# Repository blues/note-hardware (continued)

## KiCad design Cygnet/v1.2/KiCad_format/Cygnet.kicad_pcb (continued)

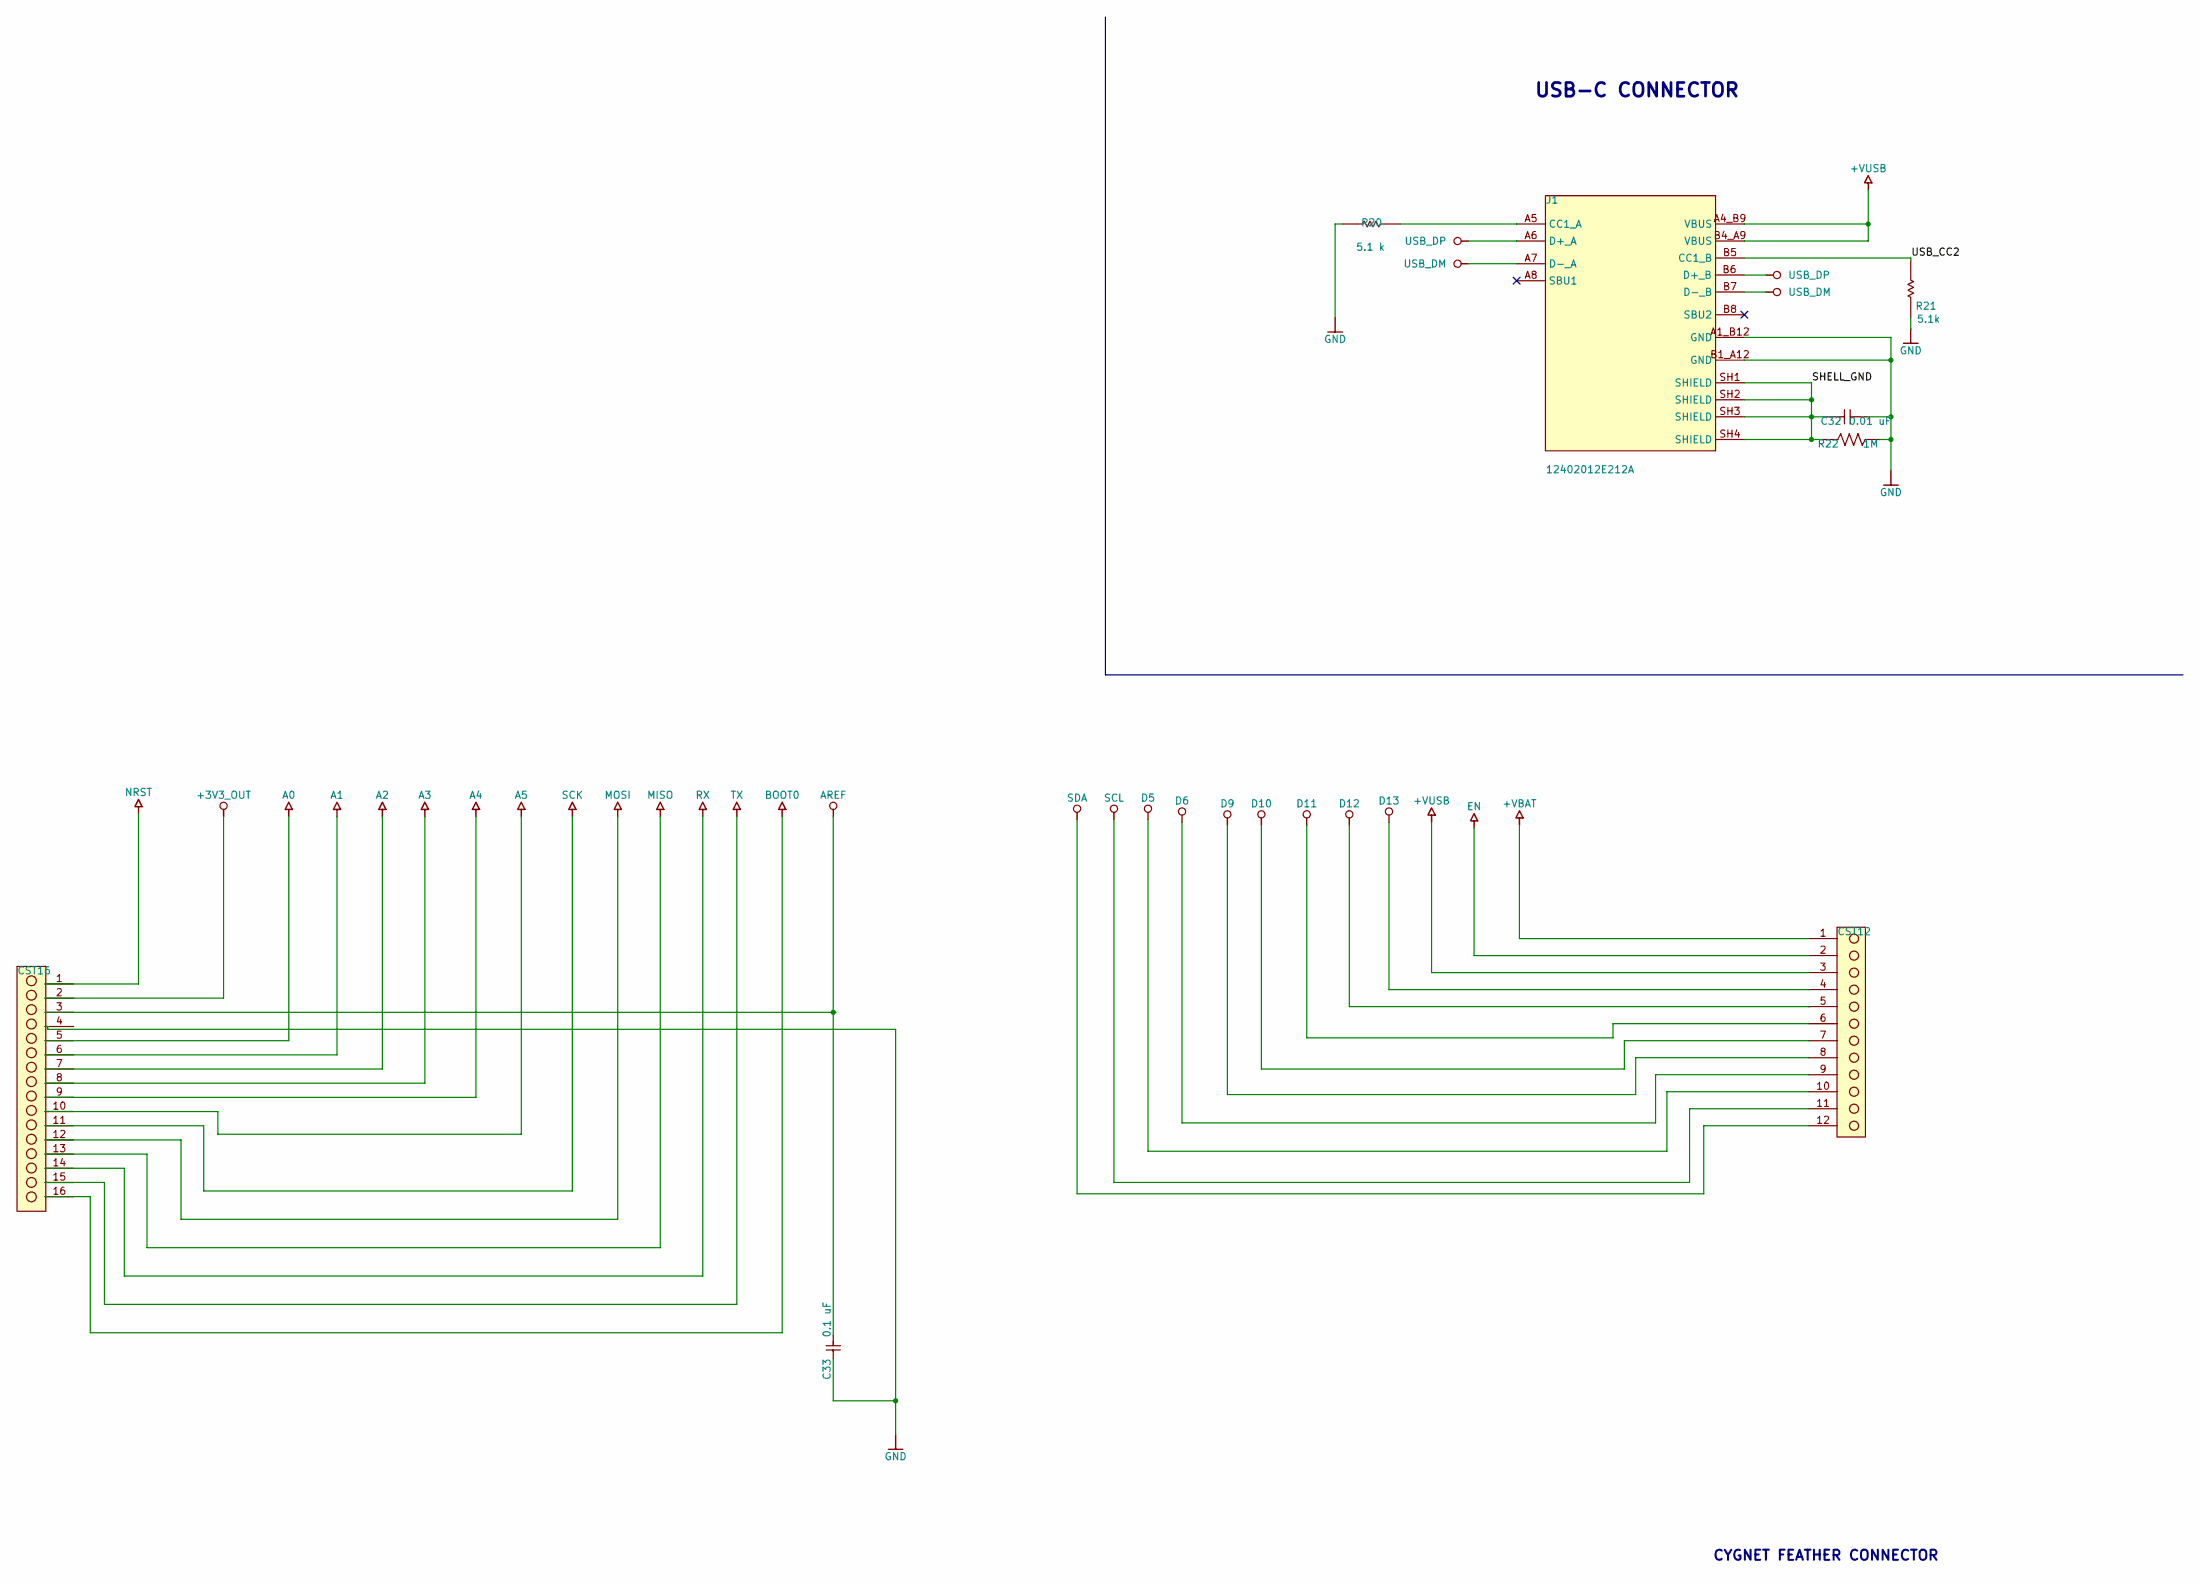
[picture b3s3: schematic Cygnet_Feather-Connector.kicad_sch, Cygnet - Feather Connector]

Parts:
C32: 0.01 uF; CS1206KKX7RCBB103-Footprint-1; MPN CS1206KKX7RCBB103
C33: 0.1 uF; FP-CC0402-MFG; MPN CC0402KRX7R7BB104
CST12: 12 pin castellated hole 1.6mm/ 1mm; 12 pin castellated hole 1.6mm_ 1mm-Footprint-1
CST16: 16 pin castellations 1.6mm/ 1mm; castellations 1mm_ 0.7mm-Footprint-1
J1: 12402012E212A; AMPHENOL_12402012E212A; MPN 12402012E212A
R20: 5.1 k; RESC1005X40X25NL05T10; MPN RC0402JR-075K1L
R21: 5.1k; RESC1005X40X25NL05T10; MPN RC0402JR-075K1L
R22: 1M; RC1206FR-071ML-Footprint-1; MPN RC1206FR-071ML

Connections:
+3V3_OUT: CST16.2; also elsewhere on the board
+VBAT: CST12.1; also elsewhere on the board
+VUSB: CST12.3, J1.A4_B9 (VBUS), J1.B4_A9 (VBUS); also elsewhere on the board
/Feather Connector/SHELL_GND: C32.1, J1.SH1 (SHIELD), J1.SH2 (SHIELD), J1.SH3 (SHIELD), J1.SH4 (SHIELD), R22.1
/Feather Connector/USB_CC2: J1.B5 (CC1_B), R21.2
A0: CST16.5; also elsewhere on the board
A1: CST16.6; also elsewhere on the board
A2: CST16.7; also elsewhere on the board
A3: CST16.8; also elsewhere on the board
A4: CST16.9; also elsewhere on the board
A5: CST16.10; also elsewhere on the board
AREF: C33.1, CST16.3; also elsewhere on the board
BOOT0: CST16.16; also elsewhere on the board
D5: CST12.10; also elsewhere on the board
D6: CST12.9; also elsewhere on the board
D9: CST12.8; also elsewhere on the board
D10: CST12.7; also elsewhere on the board
D11: CST12.6; also elsewhere on the board
D12: CST12.5; also elsewhere on the board
D13: CST12.4; also elsewhere on the board
EN: CST12.2; also elsewhere on the board
GND: C32.2, C33.2, CST16.4, J1.A1_B12 (GND), J1.B1_A12 (GND), R20.1, R21.1, R22.2; also elsewhere on the board
MISO: CST16.13; also elsewhere on the board
MOSI: CST16.12; also elsewhere on the board
NRST: CST16.1; also elsewhere on the board
unnamed: J1.A5 (CC1_A), R20.2
RX: CST16.14; also elsewhere on the board
SCK: CST16.11; also elsewhere on the board
SCL: CST12.11; also elsewhere on the board
SDA: CST12.12; also elsewhere on the board
TX: CST16.15; also elsewhere on the board
USB_DM: J1.A7 (D-_A), J1.B7 (D-_B); also elsewhere on the board
USB_DP: J1.A6 (D+_A), J1.B6 (D+_B); also elsewhere on the board

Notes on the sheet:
CYGNET FEATHER CONNECTOR
USB-C CONNECTOR

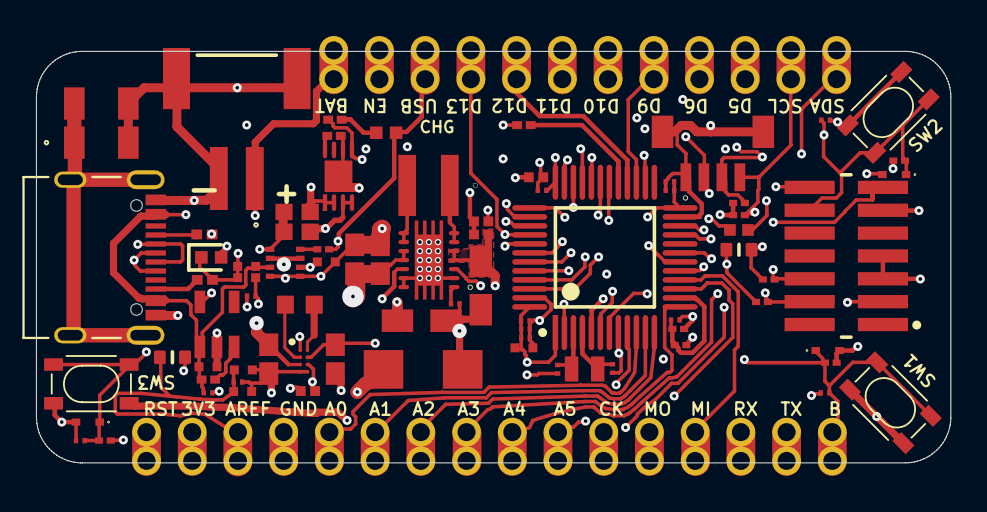
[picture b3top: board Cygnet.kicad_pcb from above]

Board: 4 copper layers, 50.8 x 22.9 mm, 80 parts (0 on the bottom side), 59 nets.

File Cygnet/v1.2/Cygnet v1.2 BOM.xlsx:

Line # | Name | Description | Designator | Quantity | Alternative Group Name | Manufacturer 1 | Manufacturer Part Number 1 | Manufacturer Lifecycle 1 | Supplier 1 | Supplier Part Number 1 | Supplier Unit Price 1 | Supplier Subtotal 1
 | PB-SKRPADE010 | Push button switch Tactile N.O. SPST (BLACK) | BOOT, USER | 2 |  | Alps Electric | SKRPADE010 | Volume Production
 | 4.7µF/ 10V | Chip Capacitor, 4.7µF +/-20%, 10V, 0603, Thickness 1 mm | C1 | 1 |  | TDK | C1608X5R1A475K/0.50 | Obsolete
 | 0.1uF/16V-X5R, 100n/ 16V-X5R, 0.1uF/ 16V-X5R | Cap Ceramic 0.1uF 16V X5R 10% Pad SMD 0201 85C T/R, Cap Ceramic 0.1uF 16V X5R 1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 | C2, C3, C4, C5, C8, C9, C14, C15, C16, C21, C28, C30 | 12 |  | Murata | GRM033R61C104KE84J | Not Recommended for New Design
 | 1uF/ 16V-X5R, 1uF/ 16V-XR5, 1u/16V-X5R | Cap Cer 1UF 16V X5R 0402 | C6, C10, C24, C25, C29, C31 | 6 |  | Holystone | C0402B105K016T
 | 10nF/ 16V-X5R | Multilayer Ceramic Capacitor, 0.01 uF, 16 V, ± 10%, X5R, 0201 [0603 Metric] | C7, C11 | 2 |  | Murata | GRM033R61C103KA12D | Volume Production
 | 4pF | GRM Series 0201 4 Ohm 50 V ±0.1 pF Tolerance C0G Multilayer Ceramic Capacitor | C12, C13 | 2 |  | Murata | GRM0335C1H4R0BA01D | Volume Production
 | 10uF/ 10V-X5R, 22u/ 10V-X5R | Multilayer Ceramic Capacitor, 10 uF, 10 V, ± 10%, X5R, 0603 [1608 Metric] | C17, C18, C22, C23 | 4 |  | Murata | GRM188R61A106KE69D | Volume Production
 | 100uF/ 6.3V | F93-BE Series 1206 100 uF ±10% 6.3 V Surface Mount J-Lead Tantalum Capacitor | C19, C20 | 2 |  | Kyocera AVX | F930J107KAABE1 | Volume Production
 | 4.7uF/ 10V-X5R | Multilayer Ceramic Capacitor, 4.7 uF, 10 V, ± 10%, X5R, 0603 [1608 Metric] | C26, C27 | 2 |  | Samsung | CL10A475KP8NNNC | Volume Production
 | 0.01 uF | Multilayer Ceramic Capacitor, 0.01 uF, 1000 V, ± 10%, X7R, 1206 [3216 Metric] C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 | C32 | 1 |  | Yageo | CS1206KKX7RCBB103 | Not Recommended for New Design
 | 0.1 uF | Multilayer Ceramic Capacitor, 0.1 uF, 25 V, ± 10%, X7R, 0402 [1005 Metric] | C33 | 1 |  | Yageo | CC0402KRX7R7BB104 | Volume Production
 | 12 pin castellated hole 1.6mm/ 1mm | 12 pin castellated hole 1.6mm/ 1mm | CST12 | 1
 | 16 pin castellations 1.6mm/ 1mm | 16 pin castellations 1.6mm/ 1mm | CST16 | 1
 | 12402012E212A | USB2.0, Type C, Top mount, CH 1.68mm, Dual Row SMT | J1 | 1 |  | Amphenol | 12402012E212A | Manual Solution
 | BM04B-SRSS-TBT(LF)(SN) | 1.0mm Pitch, Ultra-Compact, Low Profile Design, Interchangeable Shrouded Header | J4 | 1 |  | JST | BM04B-SRSS-TBT(LF)(SN) | Volume Production
 | FTSH-107-01-L-DV-K | Conn Unshrouded Header HDR 14 POS 1.27mm Solder ST Top Entry SMD Tube | J5 | 1 |  | Samtec | FTSH-107-01-L-DV-K | Volume Production
 | 1769 - JST-PH 2-PIN SMT | 1769 - JST-PH 2-PIN SMT | J6 | 1
 | 1uH | Ind Chip Power Chip Molded Multi-Layer 1uH 20% 1MHz Metal 1.3A 0603 Emboss T/R 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 | L1 | 1 |  | Taiyo Yuden | MCKK1608T1R0MN
 | 1.5uH | Inductor Power Shielded Wirewound 1.5uH 20% 100KHz 9.1A 15.8mOhm DCR 1515 Autom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 | L2 | 1 |  | Coilcraft | XFL4020-152MEC | Not Recommended for New Design
 | SML-P12U2TT86R | LED Uni-Color Red 2-Pin Chip 0402(1006Metric) T/R | LD1 | 1 |  | Rohm | SML-P12U2TT86R | Volume Production
 | SML-P12WTT86R | LED Uni-Color Yellow 2-Pin Chip 0402(1006Metric) T/R | LD2 | 1 |  | Rohm | SML-P12WTT86R | Volume Production
 | 10k | RESISTOR, THICK FILM, 10KOHM, 50MW, 1%; Resistance: 10kohm; Power Rating: 50mW;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 | R1, R2, R5, R6, R8, R9, R10 | 7 |  | Multicomp | MC0201L6F1002SE | Volume Production
 | 10M | Res Thick Film 0201 10M Ohm 1% 0.05W(1/20W) ±200ppm/°C Pad SMD Automotive T/R | R3 | 1 |  | KOA Speer | RK73H1HTTC1005F | Volume Production
 | 4.3M | Res Thick Film 0201 4.3M Ohm 1% 0.05W(1/20W) ±200ppm/C Pad SMD Automotive T/R | R4 | 1 |  | KOA Speer | RK73H1HTTC4304F | Volume Production
 | 1k | SMD Chip Resistor, 1 kOhm, ± 1%, 50 mW, 0201 [0603 Metric], Thick Film, General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 | R7, R17 | 2 |  | Vishay | CRCW02011K00FNED | Volume Production
 | 1k | Chip Resistor, 1 KOhm, +/- 1%, 63 mW, -55 to 155 degC, 0402 (1005 Metric) | R11 | 1 |  | Yageo | RC0402FR-071KL | Volume Production
 | 1M | SMD Chip Resistor, 1 MOhm, ± 1%, 50 mW, 0201 [0603 Metric], Thick Film, General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 | R12, R15 | 2 |  | Yageo | RC0201FR-071ML | Volume Production
 | 100k | SMD Chip Resistor, 100 kOhm, ± 1%, 50 mW, 0201 [0603 Metric], Thick Film, Gener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 | R13 | 1
 | 10k | RESISTOR, THICK FILM, 10KOHM, 50MW, 1%; Resistance: 10kohm; Power Rating: 50mW;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 | R14 | 1 | DO NOT POPULATE | Multicomp | MC0201L6F1002SE | Volume Production
 | 180k | CHIP RES. 180K 0201 1/20W 1% 100PPM/°C | R16 | 1 |  | Walsin Technologies | MR02X1803FAL
 | 2.8k | Res Thick Film 0201 2.8K Ohm 1% 1/20W ±100ppm/°C Molded SMD SMD Paper T/R | R18 | 1 |  | Vishay Dale | CRCW02012K80FKED | Volume Production
 | 8.2M | 0201 (0603METRIC) Fixed Resistor Crcw 0.024LX0.012W 0.60MMX0.30MM 0.05W 1/20W 8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 | R19 | 1 |  | Vishay Draloric | CRCW02018M20FNED | Volume Production
 | 5.1 k, 5.1k | SMD Chip Resistor, 5.1 kOhm, ± 5%, 63 mW, 0402 [1005 Metric], Thick Film, Gener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 | R20, R21 | 2 |  | Yageo | RC0402JR-075K1L | Volume Production
 | 1M | SMD Chip Resistor, 1 MOhm, ± 1%, 250 mW, 1206 [3216 Metric], Thick Film, Genera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 | R22 | 1 |  | Yageo | RC1206FR-071ML | Volume Production
 | Jumper 0603 | Jumper 0603 | R23 | 1
 | PB-SKRPABE010 | Push button switch tactile N.O. SPST (WHITE) | RST | 1 |  | Alps Electric | SKRPABE010 | Volume Production
 | ESD5Z3.3T1G | TVS DIODE 3.3V 14.1V SOD523 | TVS1, TVS2, TVS3 | 3 |  | ON Semiconductor | ESD5Z3.3T1G | Volume Production
 | SM6T6V8A | TVS DIODE 5.8VWM 13.4VC SMB | TVS4 | 1 |  | STMicroelectronics | SM6T6V8A | Volume Production
 | STM32L433 | Ultra-low-power with FPU ARM Cortex-M4 MCU 80 MHz with 256 Kbytes Flash, USB FS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 | U1 | 1 |  | STMicroelectronics | STM32L433CCT6 | Volume Production
 | TPS63020DSJT | High Efficiency Single Inductor Buck-Boost Converter with 4A Switch 14-VSON -40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 | U2 | 1 |  | Texas Instruments | TPS63020DSJT | Volume Production
 | ISL9122AIINZ-T | Isl9122A 3.3V Ultra Low Iq Buck-Boost Regulator W/ Bypass, / Tape & Reel Rohs C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 | U3 | 1 |  | Renesas | ISL9122AIINZ-T
 | LM66200DRLR | 1.6-V to 5.5-V, 40-mΩ, 2.5-A, low-IQ, dual ideal diode 8-SOT-5X3 -40 to 125 | U4 | 1 |  | Texas Instruments | LM66200DRLR | Volume Production
 | MCP73831-2ACI/MC | Dfn Tiny Integrated Li-Ion/li-Poly Charge Mgnt Controller, 4.2V Vreg Out Rohs C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 | U5 | 1 |  | Microchip | MCP73831-2ACI/MC | Volume Production
 | AP2139AK-3.3TRG1 | 250mA 3.3V Ultra Low IQ LDO Reg. SOT23-5 | U6 | 1
 | ABS06-107-32.768KHZ-T | Crystal 0.032768MHz ±20ppm (Tol) ±250ppm (Stability) 4.1pF Flexural 80000Ohm 2-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 | Y1 | 1 |  | Abracon | ABS06-107-32.768KHZ-T | Volume Production

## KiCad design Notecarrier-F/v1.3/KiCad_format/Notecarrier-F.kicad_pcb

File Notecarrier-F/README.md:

# Notecarrier F

  - Schematics
  - Bills of material
  - PCB layouts and Gerber files
  - Dimensioned drawings
  - 3D models
  - Altium Designer sources ([v1.5/Altium](v1.5/Altium), [v1.3/Altium](v1.3/Altium))
  - KiCad design files
    - [v1.5/KiCad_format](v1.5/KiCad_format) — complete schematic + PCB, imported from the Altium sources in [v1.5/Altium](v1.5/Altium) and validated against the released fab package, BOM and pick-and-place files; see its [Porting-Notes](v1.5/KiCad_format/documentation/Porting-Notes.md)
    - [v1.3/KiCad_format](v1.3/KiCad_format) — complete schematic + PCB, imported from the release-day Altium sources in [v1.3/Altium](v1.3/Altium) and validated against the released fab package, BOM and pick-and-place file; see its [Porting-Notes](v1.3/KiCad_format/documentation/Porting-Notes.md)

## Revisions

| Folder | Board silkscreen | Byte Lab schematic | BOM | Notes |
|---|---|---|---|---|
| [v1.5](v1.5) | NOTECARRIER-F V1.5 | 100275 Rev 13 (2026-01-26) | 3001-069-001 | USB-C connector; AUX/DFU switch removed (automatic Outboard DFU routing); Feather USB feeds VUSB; VSOLAR pin wired to the solar connector; copper keepout under the Notecard antenna area |
| [v1.3](v1.3) | NOTECARRIER-F V1.3 | 100275 Rev 11 (2023-07-10) | 3000-653-002 | Micro-USB; three DIP switches |
| [v1.0](v1.0) | — | n21-evt (2022) | — | Original release |

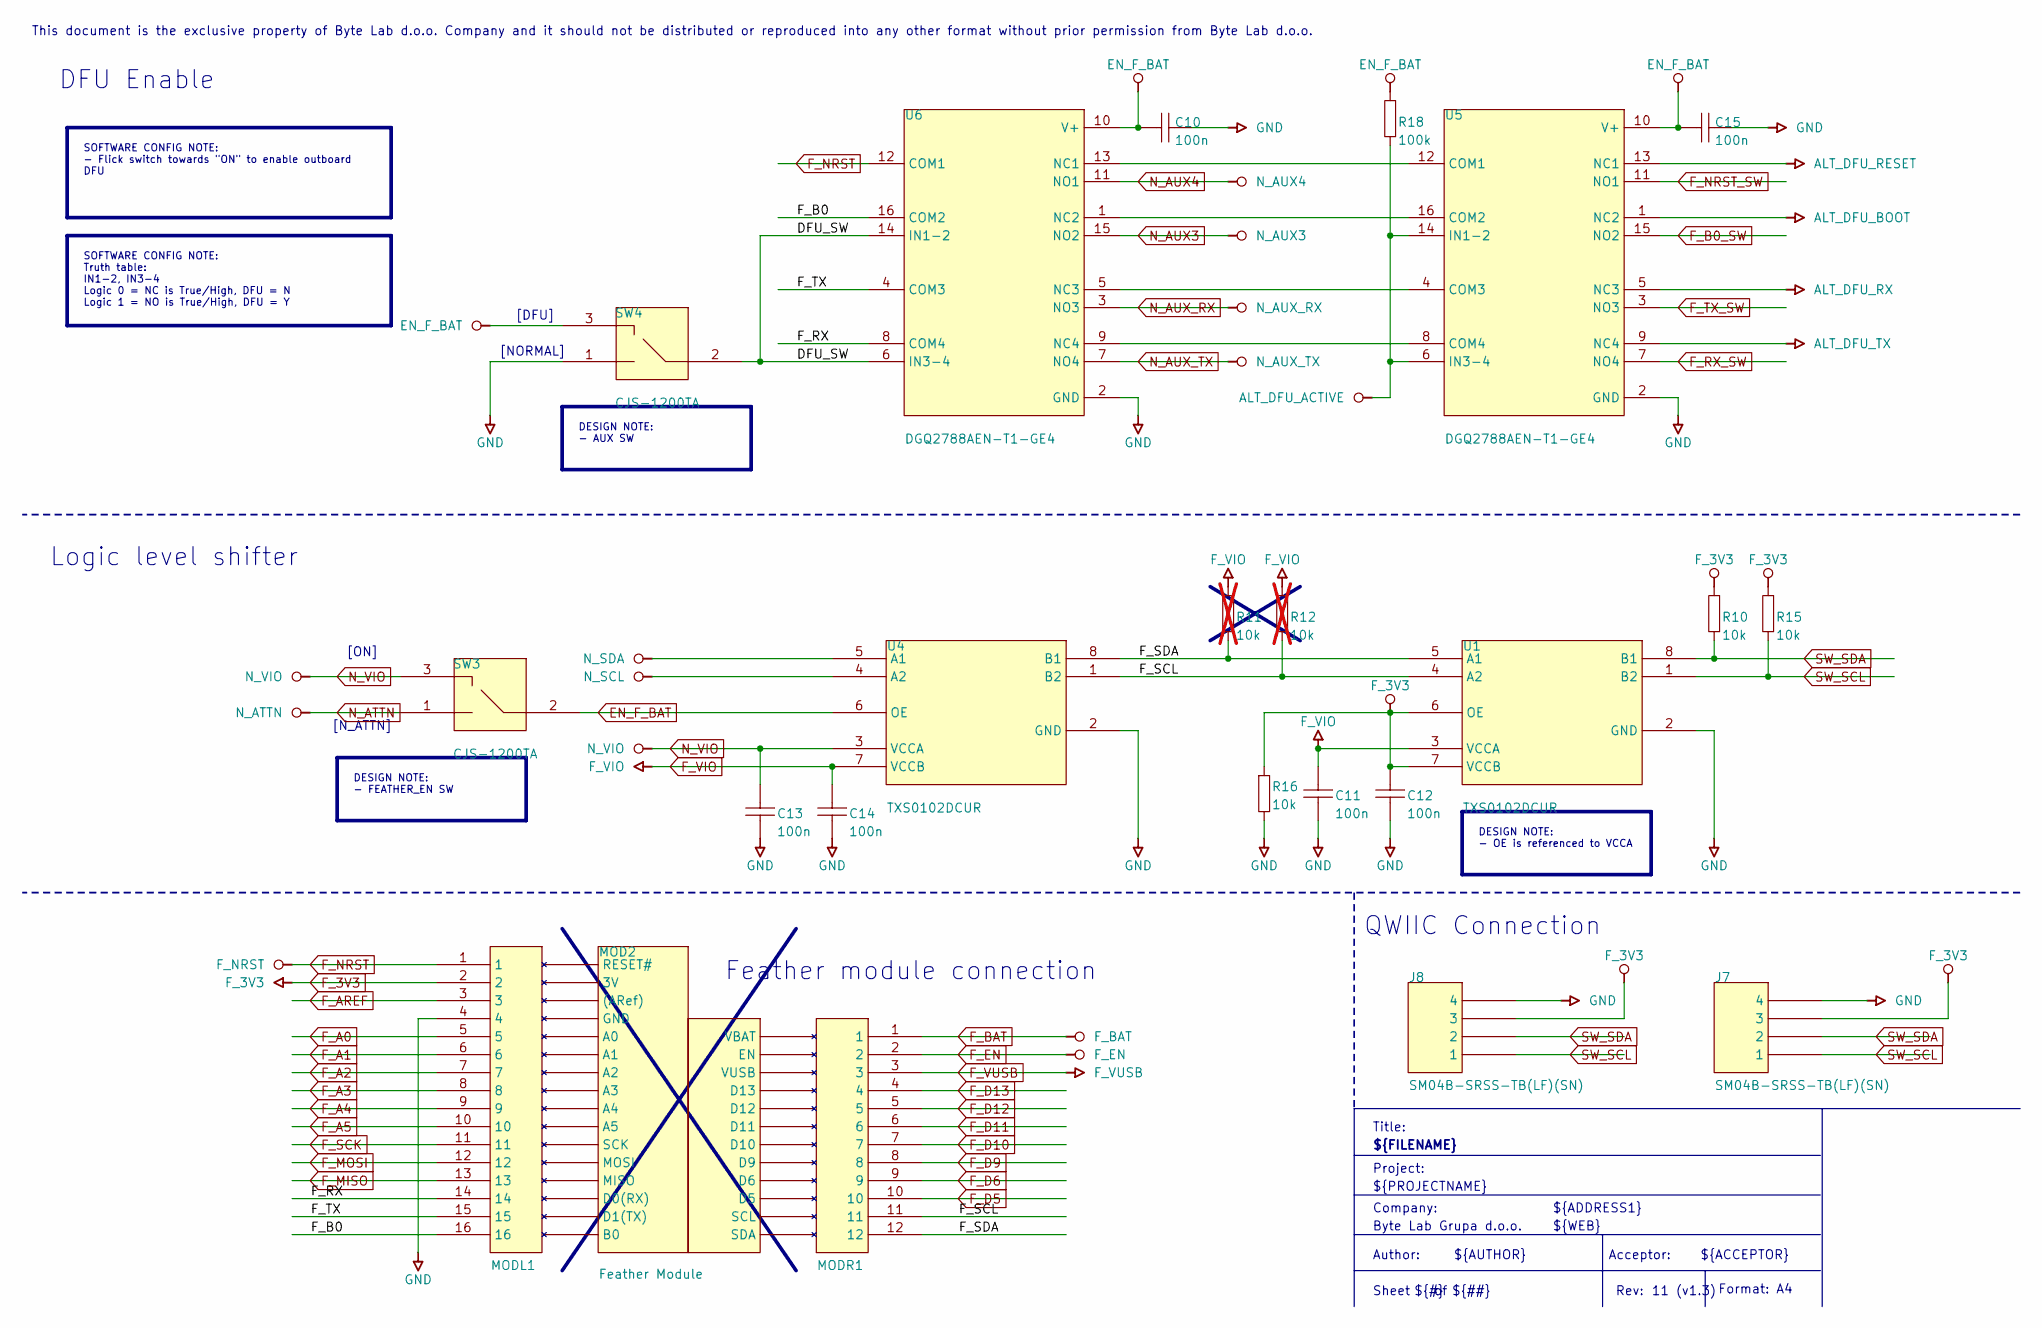
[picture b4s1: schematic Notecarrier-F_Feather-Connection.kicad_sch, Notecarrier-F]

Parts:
C10, C11, C12, C13, C14, C15: 100n; C-0402; MANUFACTURER PART NUMBER N/A
J7, J8: SM04B-SRSS-TB(LF)(SN); JST SM04B-SRSS-TB; MANUFACTURER PART NUMBER SM04B-SRSS-TB(LF)(SN)
MOD2: Feather Module; BLUES_WIRELESS_SWAN_2-54_HEADERS
MODL1: CES-116-01-L-S; 16PIN_254MM; MANUFACTURER PART NUMBER CES-116-01-L-S
MODR1: CES-112-01-L-S; 12PIN_254MM; MANUFACTURER PART NUMBER CES-112-01-L-S
R10, R15, R16: 10k; R-0402; MANUFACTURER PART NUMBER N/A
R11, R12: 10k; R-0402; MANUFACTURER PART NUMBER N/A; not fitted
R18: 100k; R-0402; MANUFACTURER PART NUMBER N/A
SW3, SW4: CJS-1200TA; SW_CJS-1200TA; MANUFACTURER PART NUMBER CJS-1200TA
U1, U4: TXS0102DCUR; SOP50P310X90-8N; MANUFACTURER PART NUMBER TXS0102DCUR
U5, U6: DGQ2788AEN-T1-GE4; QFN40P260X180X60-16N; MANUFACTURER PART NUMBER DGQ2788AEN-T1-GE4

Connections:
/Feather Connection/DFU_SW: SW4.2, U6.6 (IN3-4), U6.14 (IN1-2)
/Feather Connection/F_B0: MODL1.16, U6.16 (COM2)
/Feather Connection/F_RX: MODL1.14, U6.8 (COM4)
/Feather Connection/F_SCL: MODR1.11, R12.1, U1.4 (A2), U4.1 (B2)
/Feather Connection/F_SDA: MODR1.12, R11.1, U1.5 (A1), U4.8 (B1)
/Feather Connection/F_TX: MODL1.15, U6.4 (COM3)
ALT_DFU_ACTIVE: R18.1, U5.6 (IN3-4), U5.14 (IN1-2); also elsewhere on the board
ALT_DFU_BOOT: U5.1 (NC2); also elsewhere on the board
ALT_DFU_RESET: U5.13 (NC1); also elsewhere on the board
ALT_DFU_RX: U5.5 (NC3); also elsewhere on the board
ALT_DFU_TX: U5.9 (NC4); also elsewhere on the board
EN_F_BAT: C10.2, C15.2, R18.2, SW3.2, SW4.3, U4.6 (OE), U5.10 (V+), U6.10 (V+); also elsewhere on the board
F_3V3: C12.1, J7.3, J8.3, MODL1.2, R10.2, R15.2, R16.1, U1.6 (OE), U1.7 (VCCB); also elsewhere on the board
F_A0: MODL1.5; also elsewhere on the board
F_A1: MODL1.6; also elsewhere on the board
F_A2: MODL1.7; also elsewhere on the board
F_A3: MODL1.8; also elsewhere on the board
F_A4: MODL1.9; also elsewhere on the board
F_A5: MODL1.10; also elsewhere on the board
F_AREF: MODL1.3; also elsewhere on the board
F_B0_SW: U5.15 (NO2); also elsewhere on the board
F_BAT: MODR1.1; also elsewhere on the board
F_D5: MODR1.10; also elsewhere on the board
F_D6: MODR1.9; also elsewhere on the board
F_D9: MODR1.8; also elsewhere on the board
F_D10: MODR1.7; also elsewhere on the board
F_D11: MODR1.6; also elsewhere on the board
F_D12: MODR1.5; also elsewhere on the board
F_D13: MODR1.4; also elsewhere on the board
F_EN: MODR1.2; also elsewhere on the board
F_MISO: MODL1.13; also elsewhere on the board
F_MOSI: MODL1.12; also elsewhere on the board
F_NRST: MODL1.1, U6.12 (COM1)
F_NRST_SW: U5.11 (NO1); also elsewhere on the board
F_RX_SW: U5.7 (NO4); also elsewhere on the board
F_SCK: MODL1.11; also elsewhere on the board
F_TX_SW: U5.3 (NO3); also elsewhere on the board
F_VIO: C11.1, C14.1, R11.2, R12.2, U1.3 (VCCA), U4.7 (VCCB); also elsewhere on the board
F_VUSB: MODR1.3; also elsewhere on the board
GND: C10.1, C11.2, C12.2, C13.2, C14.2, C15.1, J7.4, J8.4, MODL1.4, R16.2, SW4.1, U1.2 (GND), U4.2 (GND), U5.2 (GND), U6.2 (GND); also elsewhere on the board
N_ATTN: SW3.1; also elsewhere on the board
N_AUX3: U6.15 (NO2); also elsewhere on the board
N_AUX4: U6.11 (NO1); also elsewhere on the board
N_AUX_RX: U6.3 (NO3); also elsewhere on the board
N_AUX_TX: U6.7 (NO4); also elsewhere on the board
N_SCL: U4.4 (A2); also elsewhere on the board
N_SDA: U4.5 (A1); also elsewhere on the board
N_VIO: C13.1, SW3.3, U4.3 (VCCA); also elsewhere on the board
unnamed: U5.12 (COM1), U6.13 (NC1)
unnamed: U5.16 (COM2), U6.1 (NC2)
unnamed: U5.4 (COM3), U6.5 (NC3)
unnamed: U5.8 (COM4), U6.9 (NC4)
SW_SCL: J7.1, J8.1, R15.1, U1.1 (B2); also elsewhere on the board
SW_SDA: J7.2, J8.2, R10.1, U1.8 (B1); also elsewhere on the board

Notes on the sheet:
${ADDRESS1}
${#}
${##}
Format: A4
Rev:
${REVISION}
Logic level shifter
QWIIC Connection
Feather module connection
Company:
${FILENAME}
[N_ATTN]
Project:
${COMPANY}
${ACCEPTOR}
Sheet
${PROJECTNAME}
[NORMAL]
Author:
${AUTHOR}
Acceptor:
${WEB}
Title:
DFU Enable
[ON]
[DFU]
This document is the exclusive property of Byte Lab d.o.o. Company and it should not be distributed or reproduced into any other format without prior permission from Byte Lab d.o.o.
SOFTWARE CONFIG NOTE: - Flick switch towards "ON" to enable outboard DFU
DESIGN NOTE: - FEATHER_EN SW
DESIGN NOTE: - OE is referenced to VCCA
DESIGN NOTE: - AUX SW
SOFTWARE CONFIG NOTE: Truth table: IN1-2, IN3-4 Logic 0 = NC is True/High, DFU = N Logic 1 = NO is True/High, DFU = Y

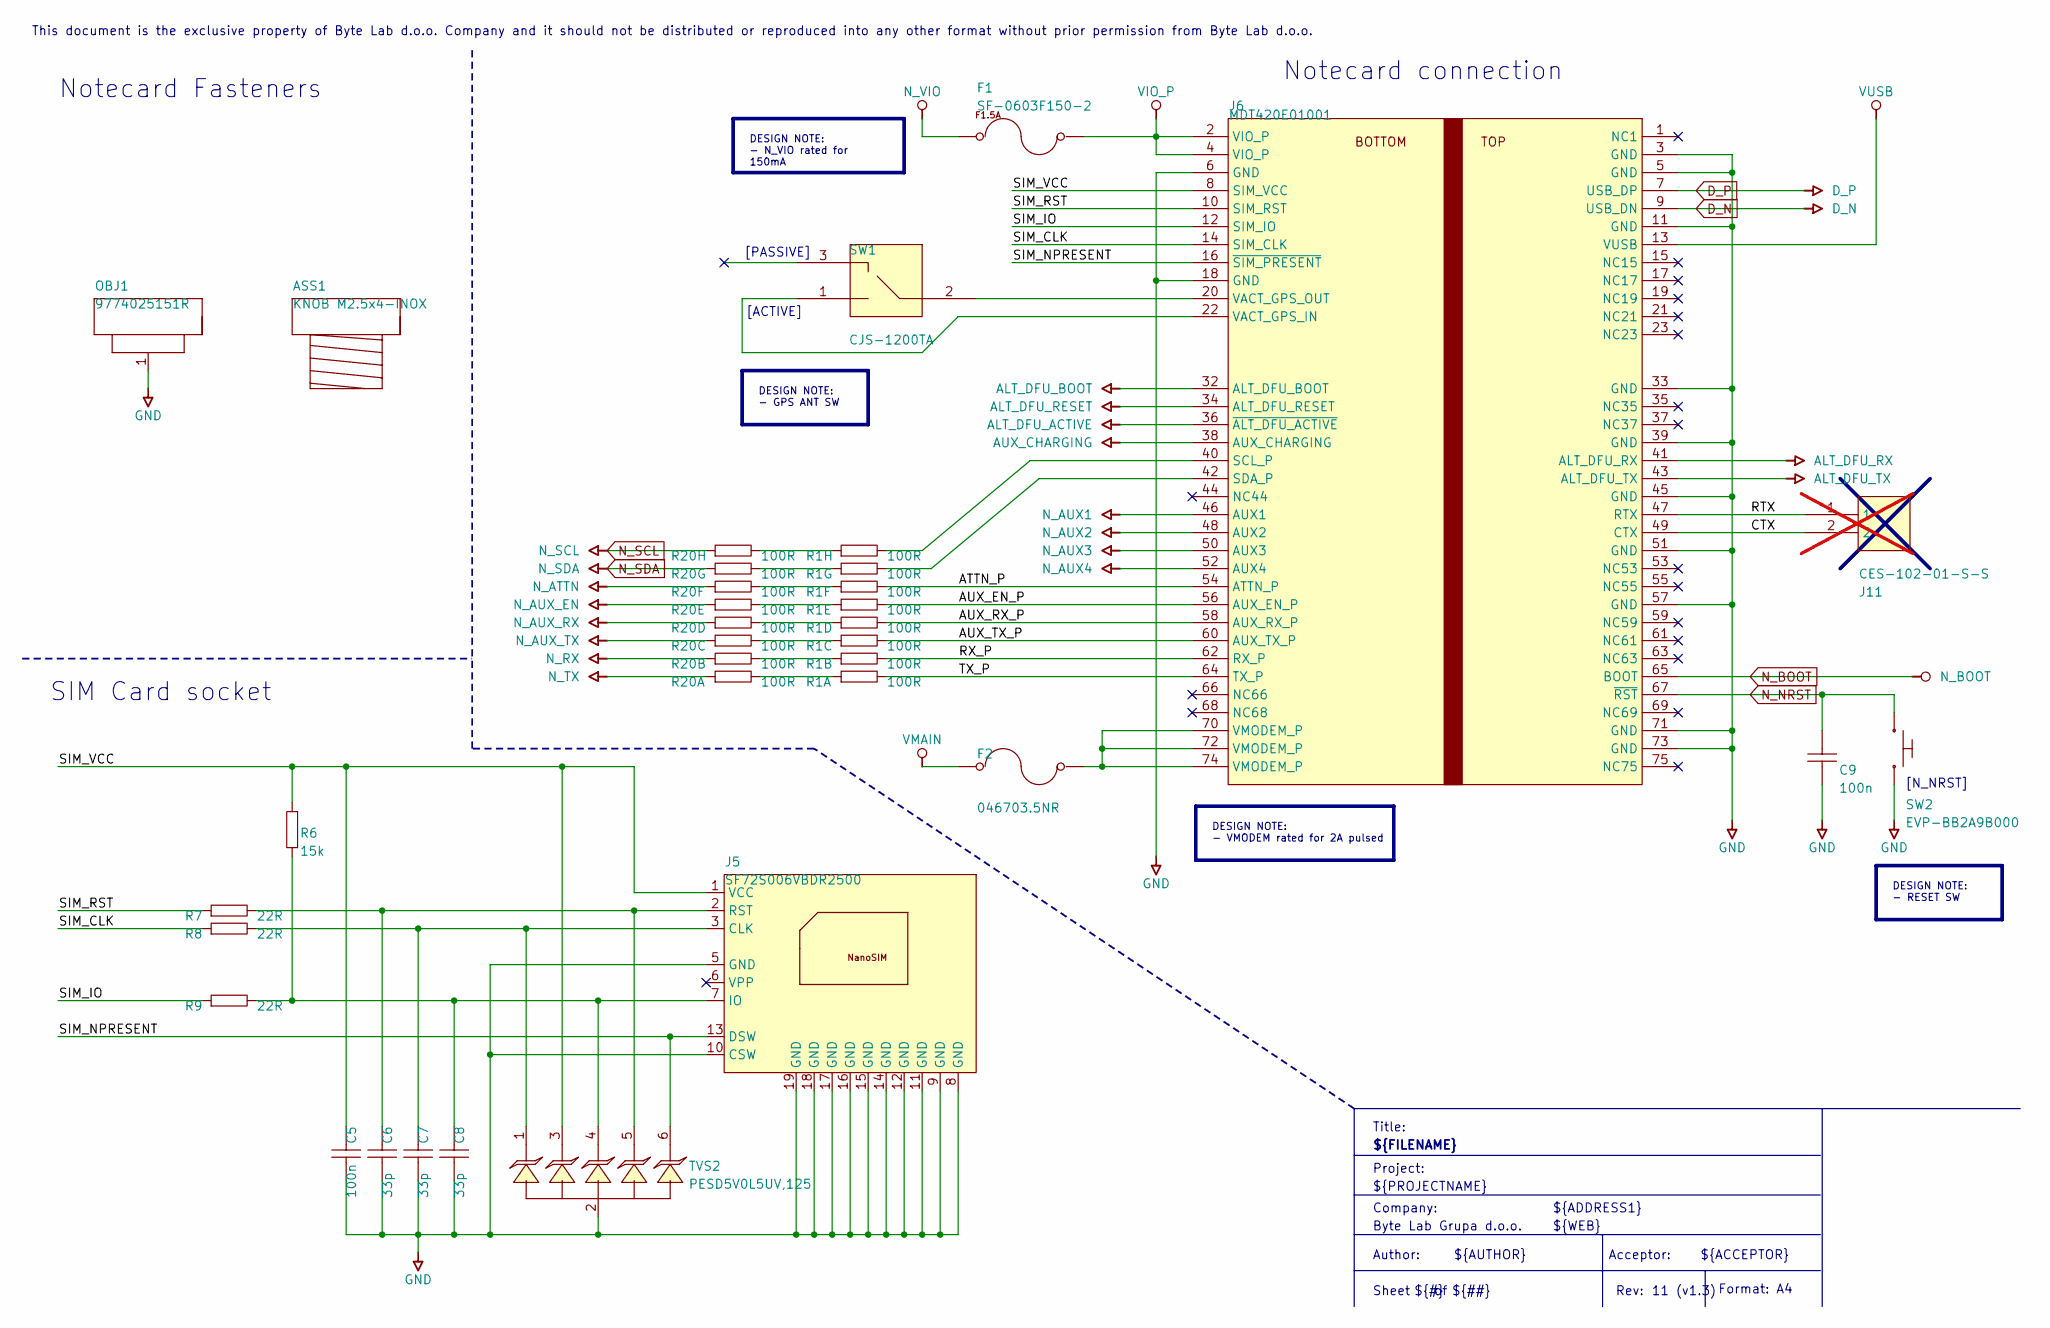
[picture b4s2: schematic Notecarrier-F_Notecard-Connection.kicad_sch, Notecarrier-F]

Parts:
ASS1: KNOB M2.5x4-INOX; MANUFACTURER PART NUMBER M2.5X4/D7985-A2
C5, C9: 100n; C-0402; MANUFACTURER PART NUMBER N/A
C6, C7, C8: 33p; C-0402; MANUFACTURER PART NUMBER N/A
F1: SF-0603F150-2; FS-0603; MANUFACTURER PART NUMBER SF-0603F150-2
F2: 046703.5NR; FS-0603; MANUFACTURER PART NUMBER 046703.5NR
J5: SF72S006VBDR2500; J-NANOSIM-SF72S006VBA; MANUFACTURER PART NUMBER SF72S006VBDR2500
J6: MDT420E01001; J-75-0050-MOS-M2; MANUFACTURER PART NUMBER MDT420E03001
J11: CES-102-01-S-S; CONN_02; MANUFACTURER PART NUMBER CES-102-01-S-S; not fitted
OBJ1: 9774025151R; DIST-WASMSIM0250; MANUFACTURER PART NUMBER 9774025151R
R1, R20: 100R; RESCAXS80P640X160X50-16N; MANUFACTURER PART NUMBER 742C163101JP
R6: 15k; R-0402; MANUFACTURER PART NUMBER N/A
R7, R8, R9: 22R; R-0402; MANUFACTURER PART NUMBER N/A
SW1: CJS-1200TA; SW_CJS-1200TA; MANUFACTURER PART NUMBER CJS-1200TA
SW2: EVP-BB2A9B000; SW_EVP-BB2A9B000; MANUFACTURER PART NUMBER EVP-BB2A9B000
TVS2: PESD5V0L5UV,125; SOT666; MANUFACTURER PART NUMBER PESD5V0L5UV,125

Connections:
/Notecard Connection/ATTN_P: J6.54 (ATTN_P), R1.11
/Notecard Connection/AUX_EN_P: J6.56 (AUX_EN_P), R1.12
/Notecard Connection/AUX_RX_P: J6.58 (AUX_RX_P), R1.13
/Notecard Connection/AUX_TX_P: J6.60 (AUX_TX_P), R1.14
/Notecard Connection/CTX: J6.49 (CTX), J11.2
/Notecard Connection/RTX: J6.47 (RTX), J11.1
/Notecard Connection/RX_P: J6.62 (RX_P), R1.15
/Notecard Connection/SIM_CLK: J6.14 (SIM_CLK), R8.1
/Notecard Connection/SIM_IO: J6.12 (SIM_IO), R9.1
/Notecard Connection/SIM_NPRESENT: J5.13 (DSW), J6.16 (~SIM_PRESENT), TVS2.6 (C6)
/Notecard Connection/SIM_RST: J6.10 (SIM_RST), R7.1
/Notecard Connection/SIM_VCC: C5.2, J5.1 (VCC), J6.8 (SIM_VCC), R6.2, TVS2.3 (C3)
/Notecard Connection/TX_P: J6.64 (TX_P), R1.16
ALT_DFU_ACTIVE: J6.36 (~ALT_DFU_ACTIVE); also elsewhere on the board
ALT_DFU_BOOT: J6.32 (ALT_DFU_BOOT); also elsewhere on the board
ALT_DFU_RESET: J6.34 (ALT_DFU_RESET); also elsewhere on the board
ALT_DFU_RX: J6.41 (ALT_DFU_RX); also elsewhere on the board
ALT_DFU_TX: J6.43 (ALT_DFU_TX); also elsewhere on the board
AUX_CHARGING: J6.38 (AUX_CHARGING); also elsewhere on the board
D_N: J6.9 (USB_DN); also elsewhere on the board
D_P: J6.7 (USB_DP); also elsewhere on the board
GND: C5.1, C6.1, C7.1, C8.1, C9.1, J5.5 (GND), J5.8 (GND), J5.9 (GND), J5.10 (CSW), J5.11 (GND), J5.12 (GND), J5.14 (GND), J5.15 (GND), J5.16 (GND), J5.17 (GND), J5.18 (GND), J5.19 (GND), J6.3 (GND), J6.5 (GND), J6.6 (GND), J6.11 (GND), J6.18 (GND), J6.33 (GND), J6.39 (GND), J6.45 (GND), J6.51 (GND), J6.57 (GND), J6.71 (GND), J6.73 (GND), OBJ1.1, SW2.2 (B), TVS2.2 (A2); also elsewhere on the board
N_ATTN: R20.6; also elsewhere on the board
N_AUX1: J6.46 (AUX1); also elsewhere on the board
N_AUX2: J6.48 (AUX2); also elsewhere on the board
N_AUX3: J6.50 (AUX3); also elsewhere on the board
N_AUX4: J6.52 (AUX4); also elsewhere on the board
N_AUX_EN: R20.5; also elsewhere on the board
N_AUX_RX: R20.4; also elsewhere on the board
N_AUX_TX: R20.3; also elsewhere on the board
N_BOOT: J6.65 (BOOT); also elsewhere on the board
N_NRST: C9.2, J6.67 (~RST), SW2.1 (A); also elsewhere on the board
N_RX: R20.2; also elsewhere on the board
N_SCL: R20.8; also elsewhere on the board
N_SDA: R20.7; also elsewhere on the board
N_TX: R20.1; also elsewhere on the board
N_VIO: F1.1; also elsewhere on the board
unnamed: F2.2, J6.70 (VMODEM_P), J6.72 (VMODEM_P), J6.74 (VMODEM_P)
unnamed: C7.2, J5.3 (CLK), R8.2, TVS2.1 (C1)
unnamed: C8.2, J5.7 (IO), R6.1, R9.2, TVS2.4 (C4)
unnamed: C6.2, J5.2 (RST), R7.2, TVS2.5 (A5)
unnamed: J6.40 (SCL_P), R1.9
unnamed: J6.42 (SDA_P), R1.10
unnamed: J6.22 (VACT_GPS_IN), SW1.1
unnamed: J6.20 (VACT_GPS_OUT), SW1.2
unnamed: R1.1, R20.16
unnamed: R1.2, R20.15
unnamed: R1.3, R20.14
unnamed: R1.4, R20.13
unnamed: R1.5, R20.12
unnamed: R1.6, R20.11
unnamed: R1.7, R20.10
unnamed: R1.8, R20.9
VIO_P: F1.2, J6.2 (VIO_P), J6.4 (VIO_P)
VMAIN: F2.1; also elsewhere on the board
VUSB: J6.13 (VUSB); also elsewhere on the board

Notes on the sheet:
${AUTHOR}
Title:
Rev:
Sheet
Acceptor:
${FILENAME}
${REVISION}
[ACTIVE]
Notecard connection
Author:
${#}
Project:
${##}
[PASSIVE]
Format: A4
${COMPANY}
This document is the exclusive property of Byte Lab d.o.o. Company and it should not be distributed or reproduced into any other format without prior permission from Byte Lab d.o.o.
SIM Card socket
${WEB}
Notecard Fasteners
${ADDRESS1}
${PROJECTNAME}
Company:
[N_NRST]
${ACCEPTOR}
DESIGN NOTE: - N_VIO rated for 150mA
DESIGN NOTE: - GPS ANT SW
DESIGN NOTE: - RESET SW
DESIGN NOTE: - VMODEM rated for 2A pulsed
